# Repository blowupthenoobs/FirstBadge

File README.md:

Trying my hand at making a PCB badge to claim a water bottle in hack club fallout. Has some introductory information for myself and a fun little shooting animation because I had to make my PCB actually do something, you know?

## project by blowupthenoobs
###### also very many thanks to onlythebest for walking me through this, lol

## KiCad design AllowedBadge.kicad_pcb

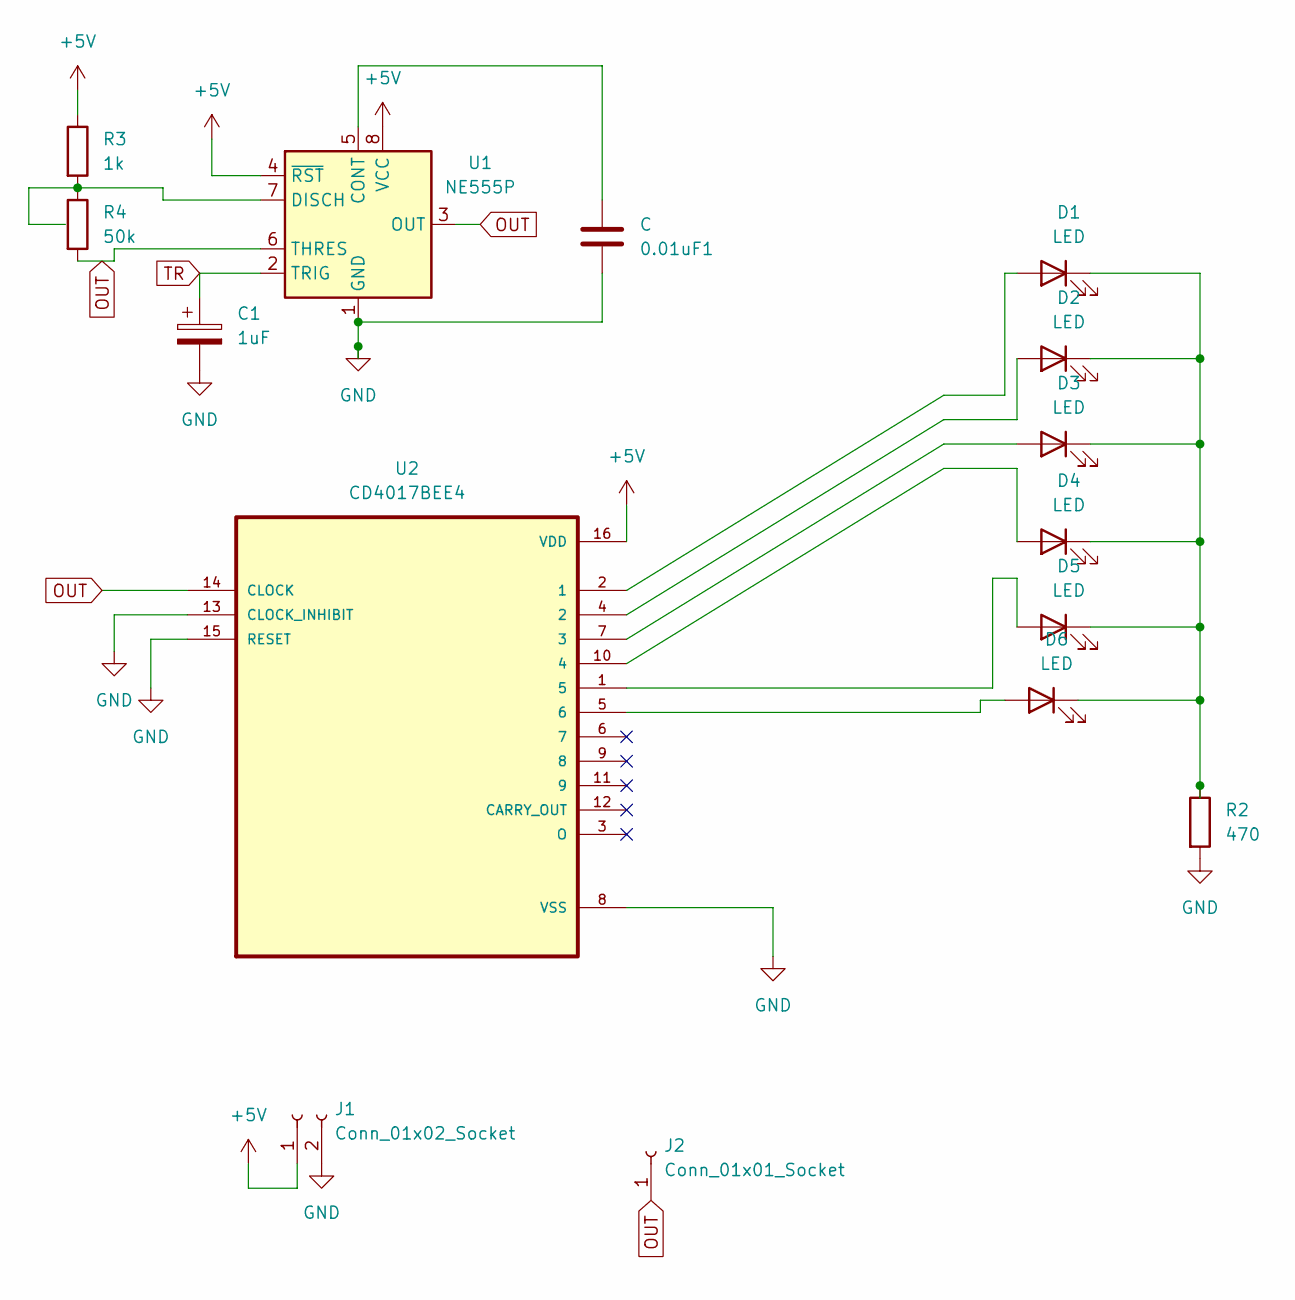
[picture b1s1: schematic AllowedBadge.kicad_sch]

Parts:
0.01uF1: C; C_Disc_D7.5mm_W2.5mm_P5.00mm
C1: 1uF; CP_Radial_D5.0mm_P2.00mm
D1, D2, D3, D4, D5, D6: LED; LED_D5.0mm
J1: Conn_01x02_Socket; PinHeader_1x02_P2.54mm_Vertical
J2: Conn_01x01_Socket; PinHeader_1x01_P2.54mm_Vertical
R2: 470; R_Axial_DIN0207_L6.3mm_D2.5mm_P7.62mm_Horizontal
R3: 1k; R_Axial_DIN0207_L6.3mm_D2.5mm_P7.62mm_Horizontal
R4: 50k; Potentiometer_Vishay_T93YA_Vertical
U1: NE555P; DIP-8_W7.62mm
U2: CD4017BEE4; DIP794W45P254L1969H508Q16

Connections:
+5V: J1.1, R3.1, U1.4 (~RST), U1.8 (VCC), U2.16 (VDD)
GND: 0.01uF1.1, C1.2, J1.2, R2.2, U1.1 (GND), U2.8 (VSS), U2.13 (CLOCK_INHIBIT), U2.15 (RESET)
unnamed: D1.2 (A), U2.2 (1)
unnamed: D1.1 (K), D2.1 (K), D3.1 (K), D4.1 (K), D5.1 (K), D6.1 (K), R2.1
unnamed: D2.2 (A), U2.4 (2)
unnamed: D3.2 (A), U2.7 (3)
unnamed: D4.2 (A), U2.10 (4)
unnamed: D5.2 (A), U2.1 (5)
unnamed: D6.2 (A), U2.5 (6)
unnamed: 0.01uF1.2, U1.5 (CONT)
unnamed: R3.2, R4.1, U1.7 (DISCH)
OUT: J2.1 (Pin_1_1), R4.2, U1.3 (OUT), U1.6 (THRES), U2.14 (CLOCK)
TR: C1.1, U1.2 (TRIG)

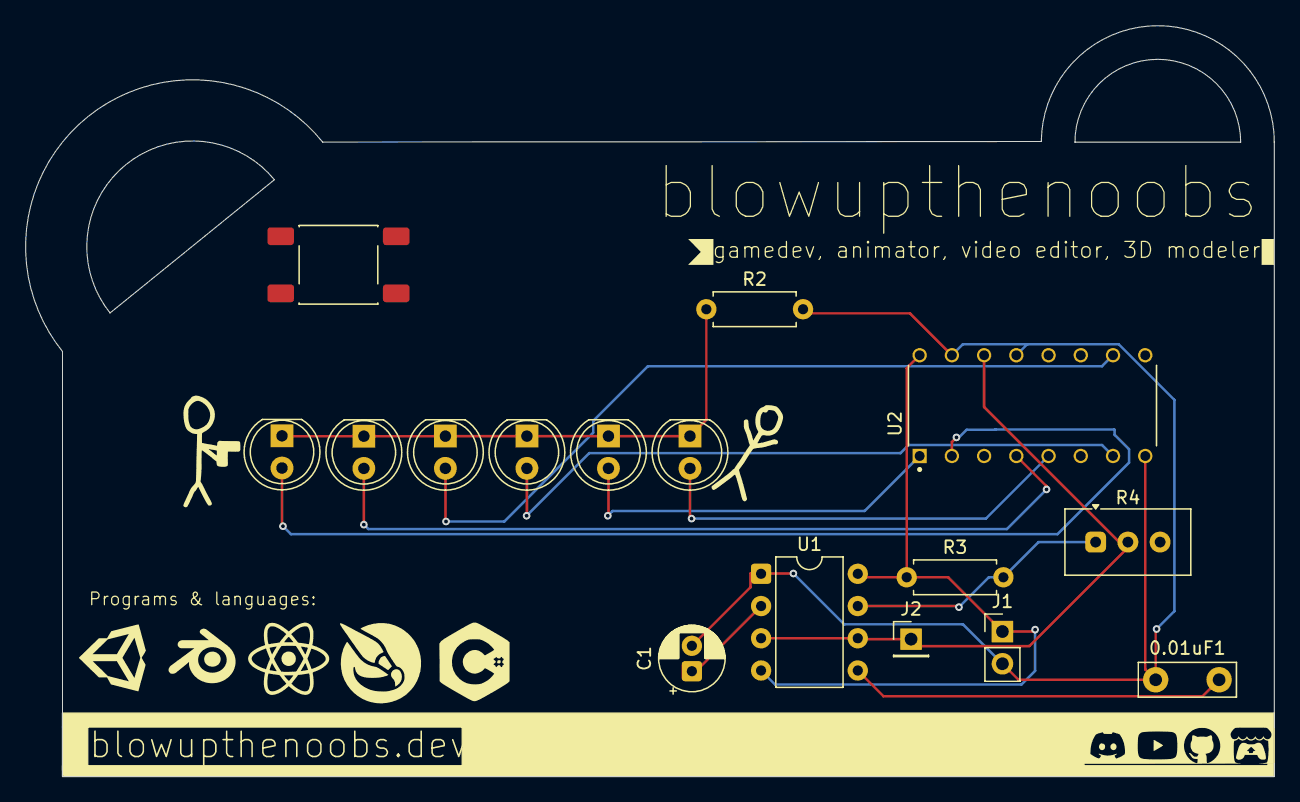
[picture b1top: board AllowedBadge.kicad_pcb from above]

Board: 2 copper layers, 98.4 x 59.2 mm, 15 parts (0 on the bottom side), 13 nets.
